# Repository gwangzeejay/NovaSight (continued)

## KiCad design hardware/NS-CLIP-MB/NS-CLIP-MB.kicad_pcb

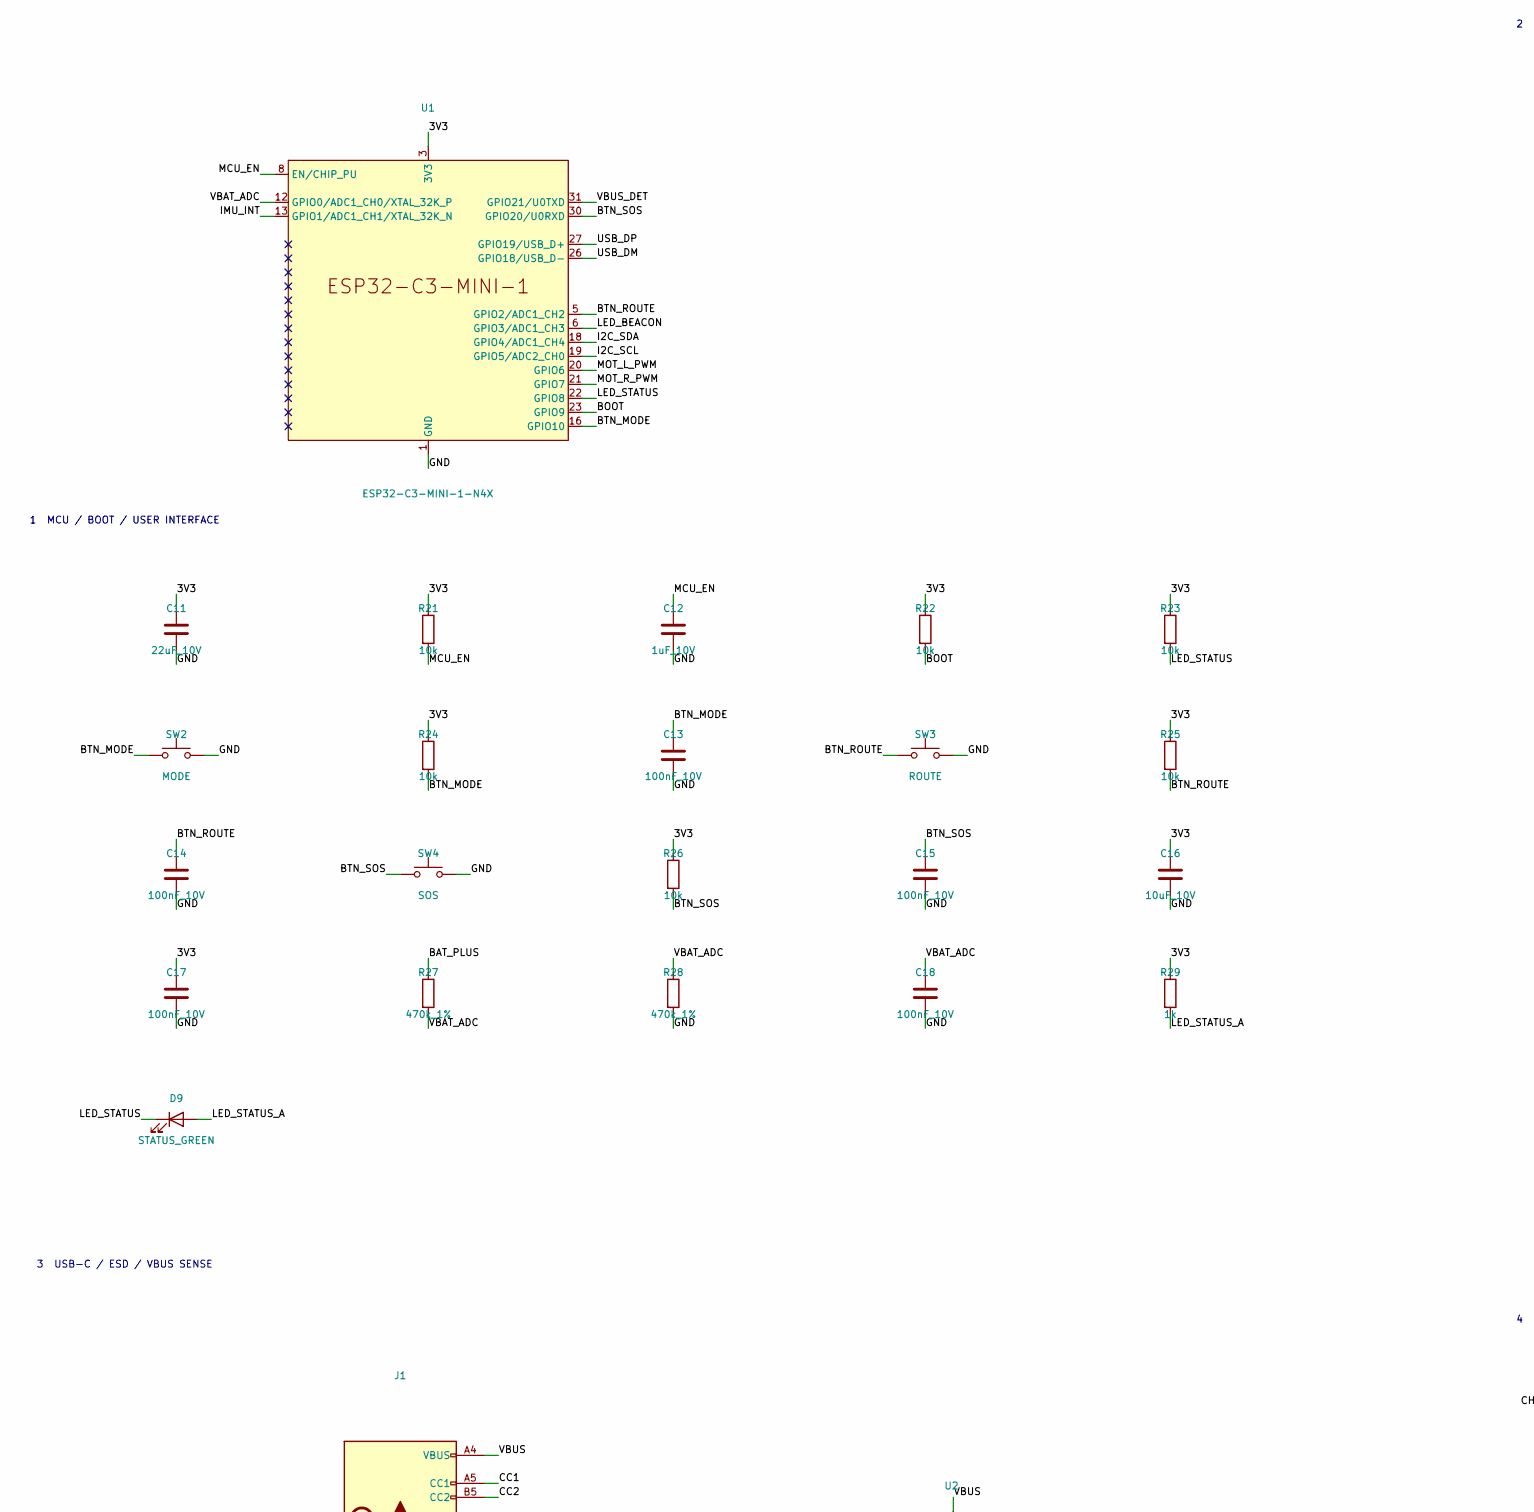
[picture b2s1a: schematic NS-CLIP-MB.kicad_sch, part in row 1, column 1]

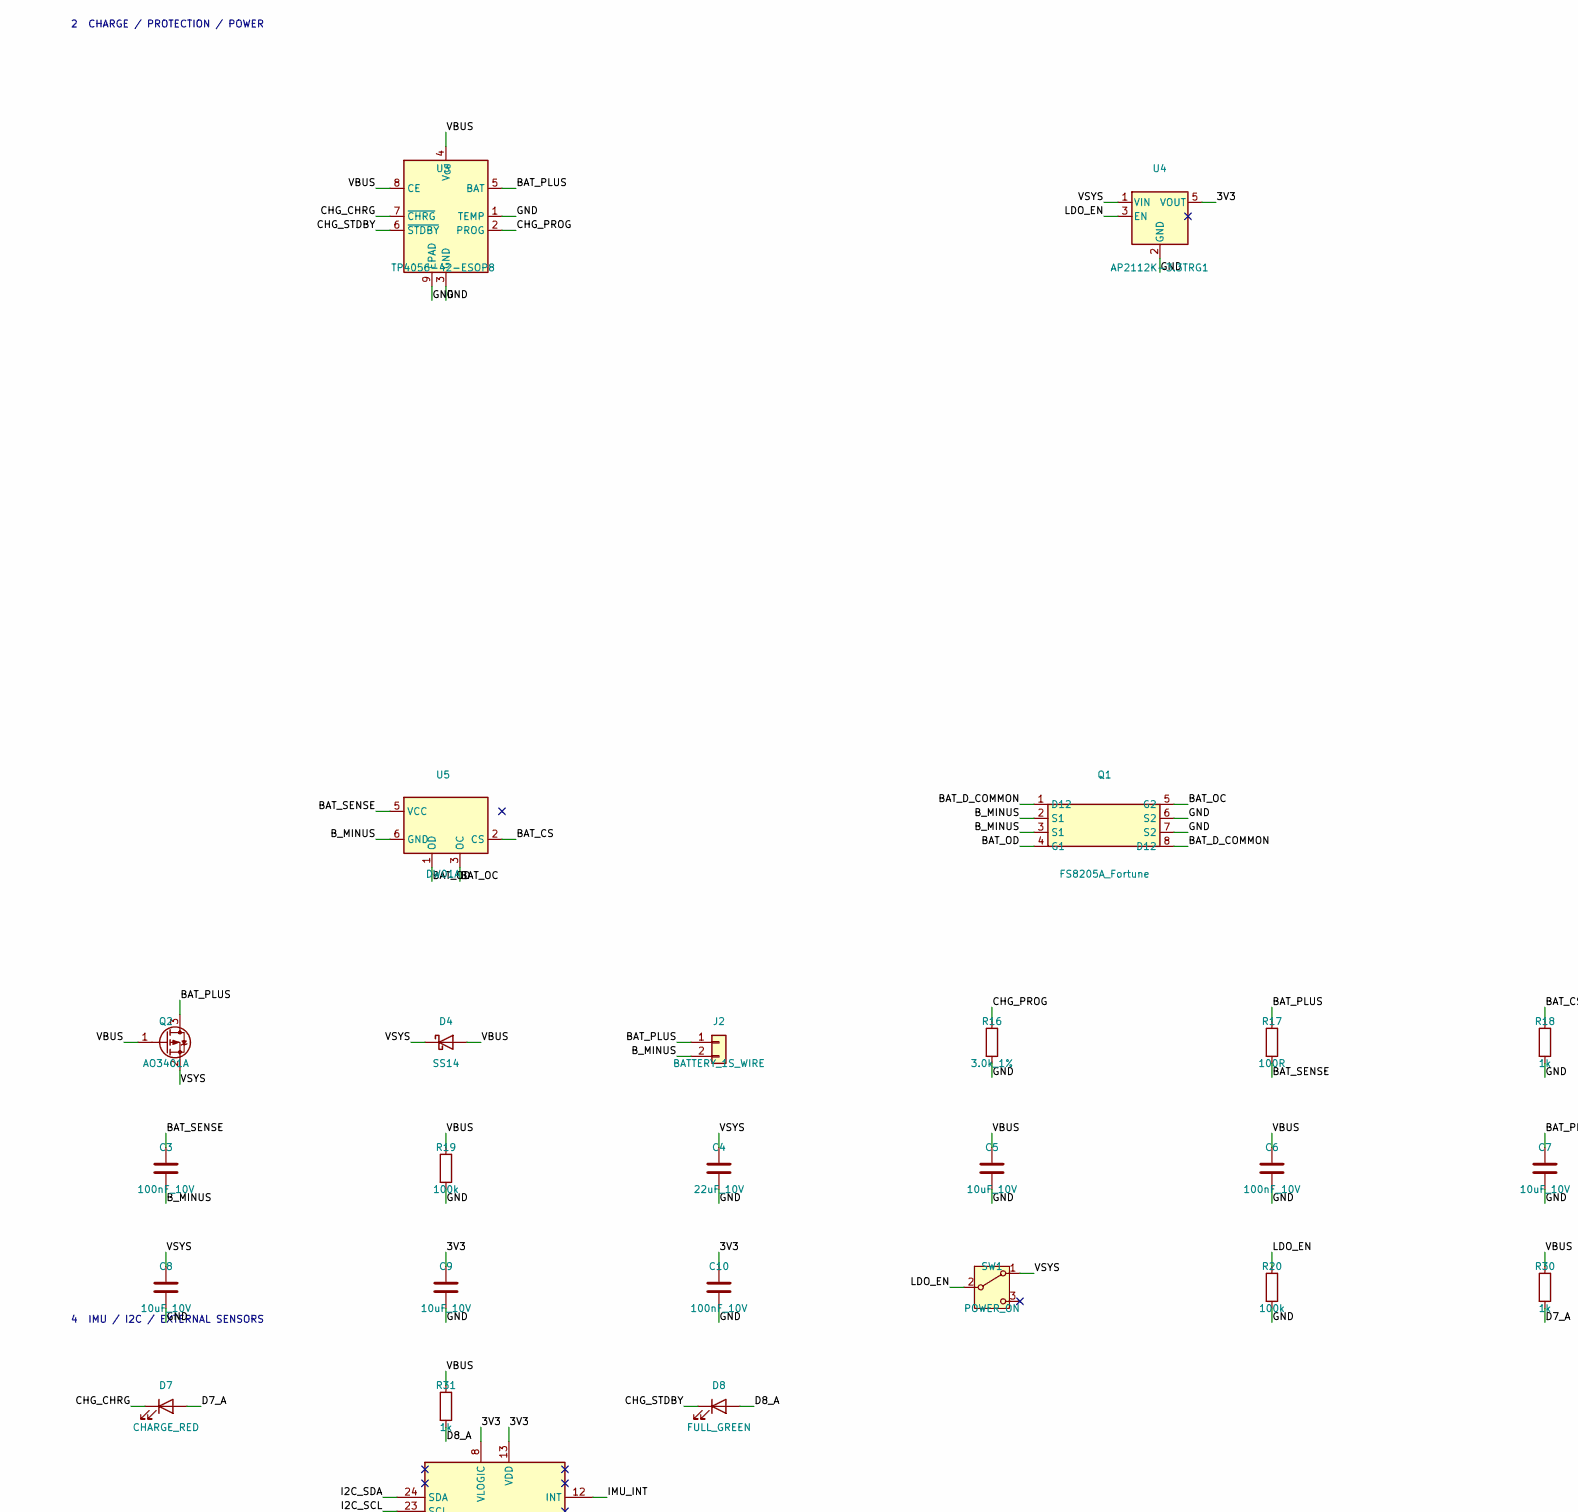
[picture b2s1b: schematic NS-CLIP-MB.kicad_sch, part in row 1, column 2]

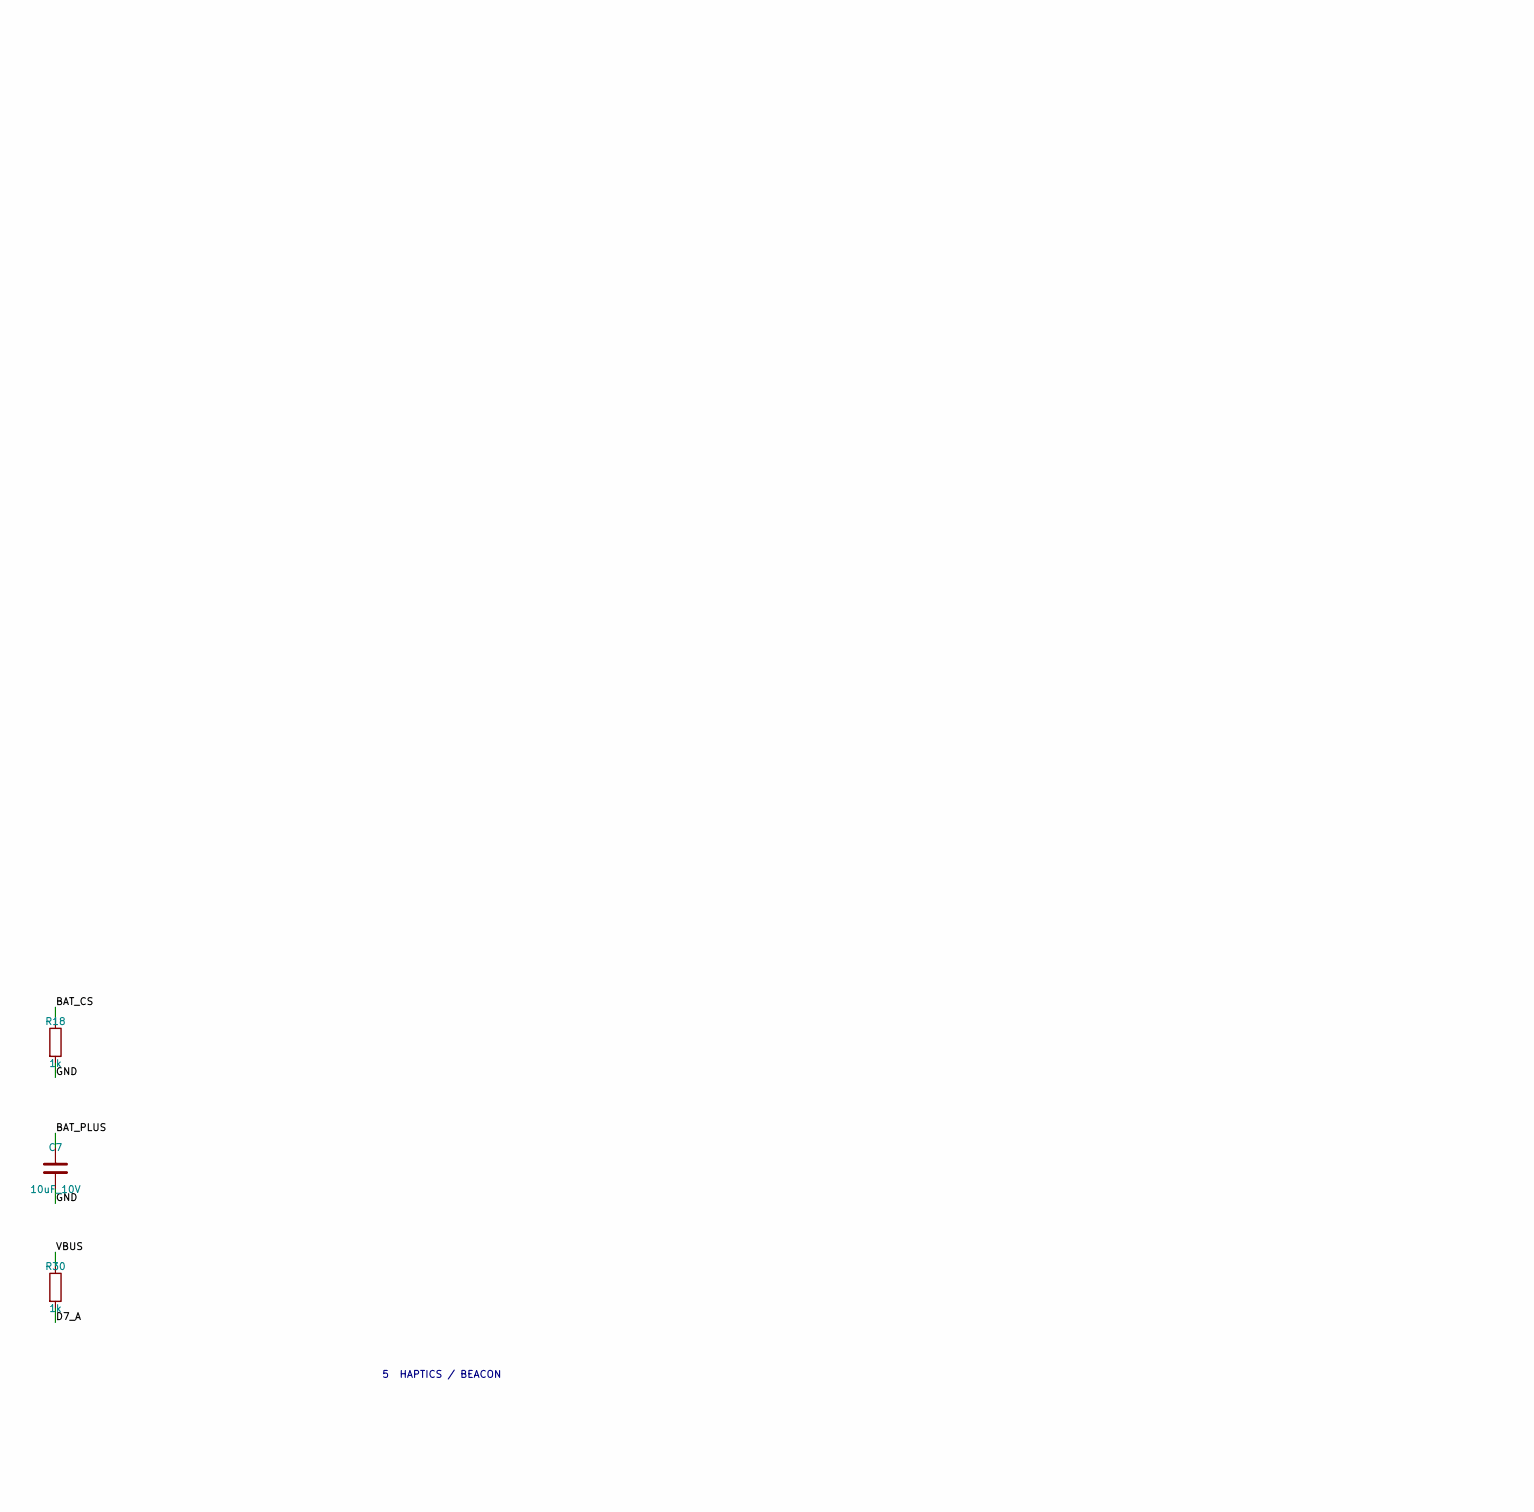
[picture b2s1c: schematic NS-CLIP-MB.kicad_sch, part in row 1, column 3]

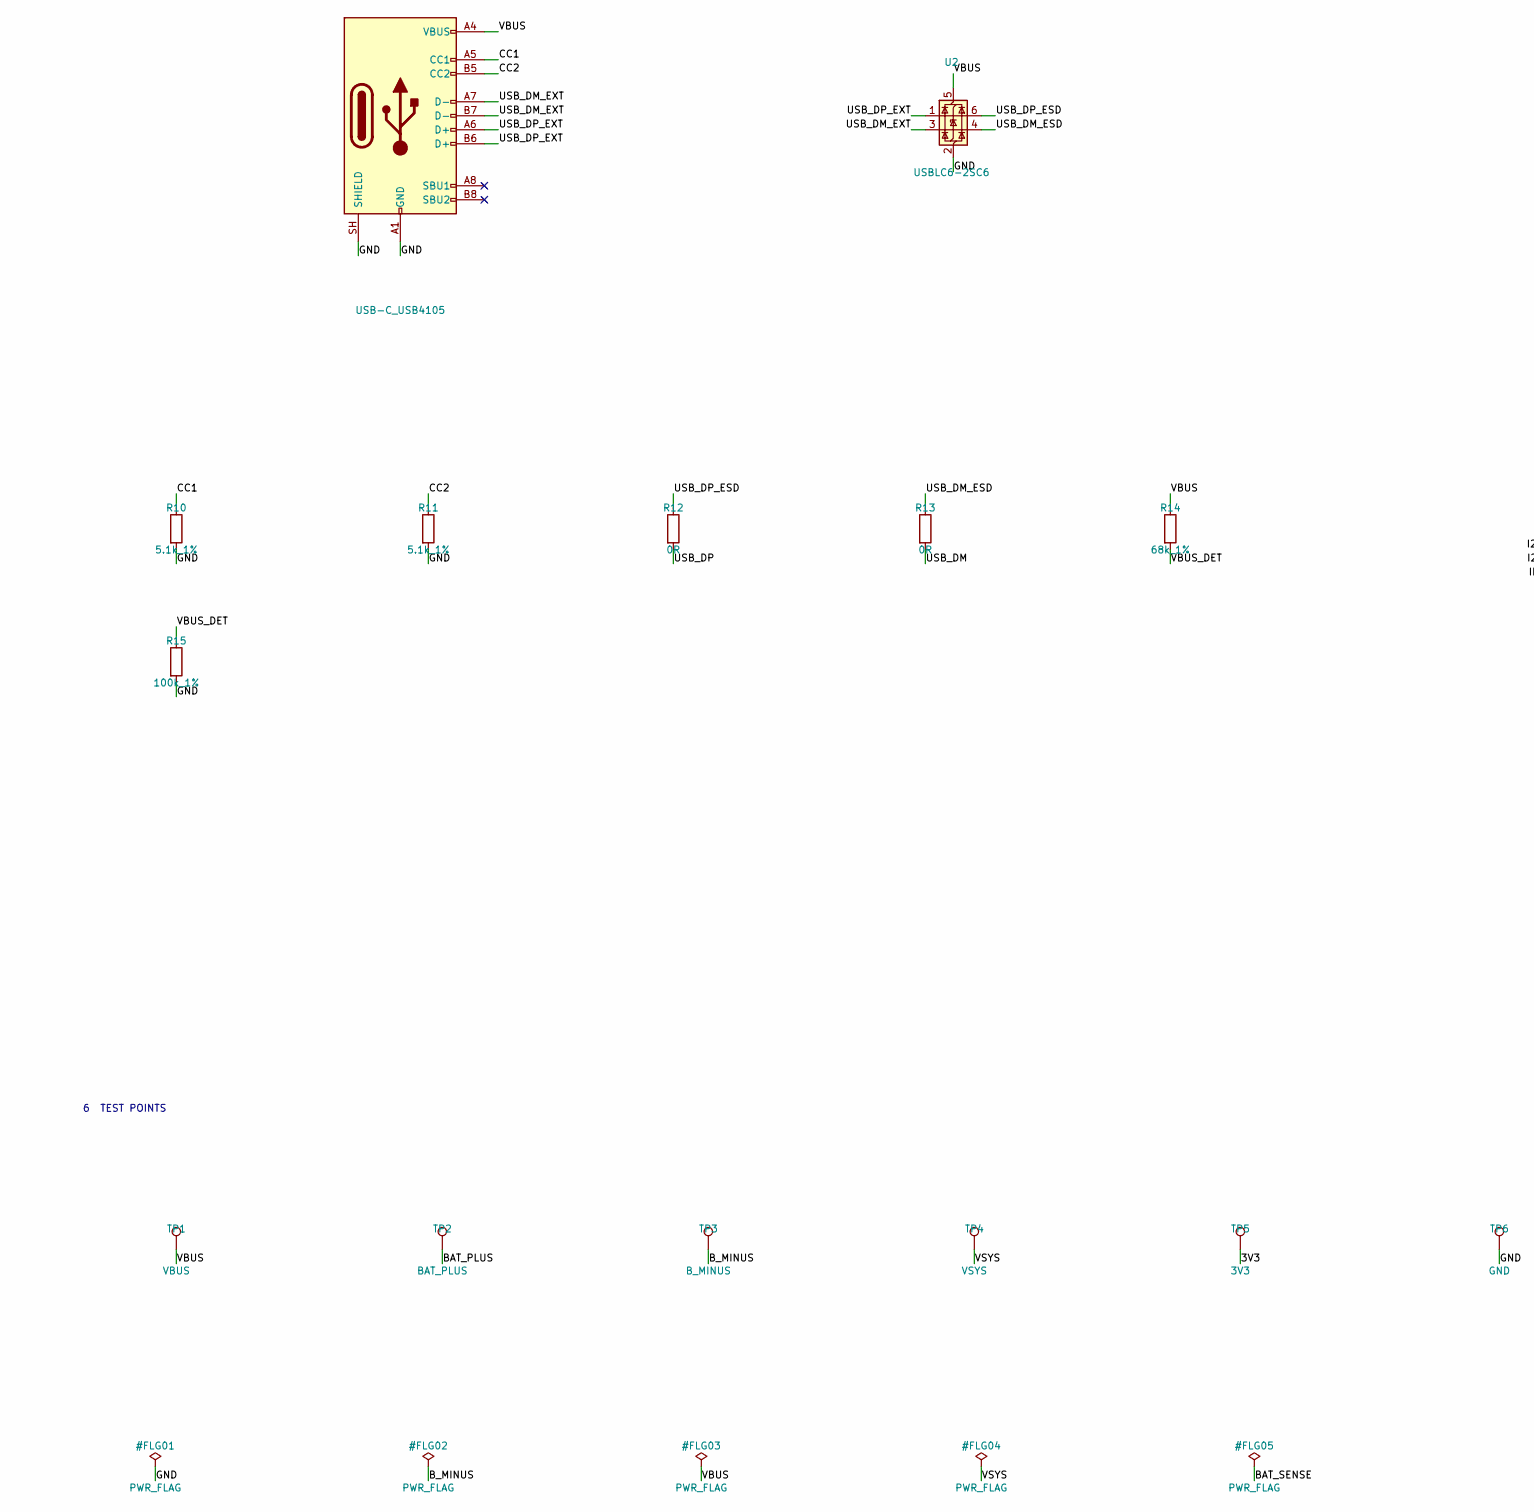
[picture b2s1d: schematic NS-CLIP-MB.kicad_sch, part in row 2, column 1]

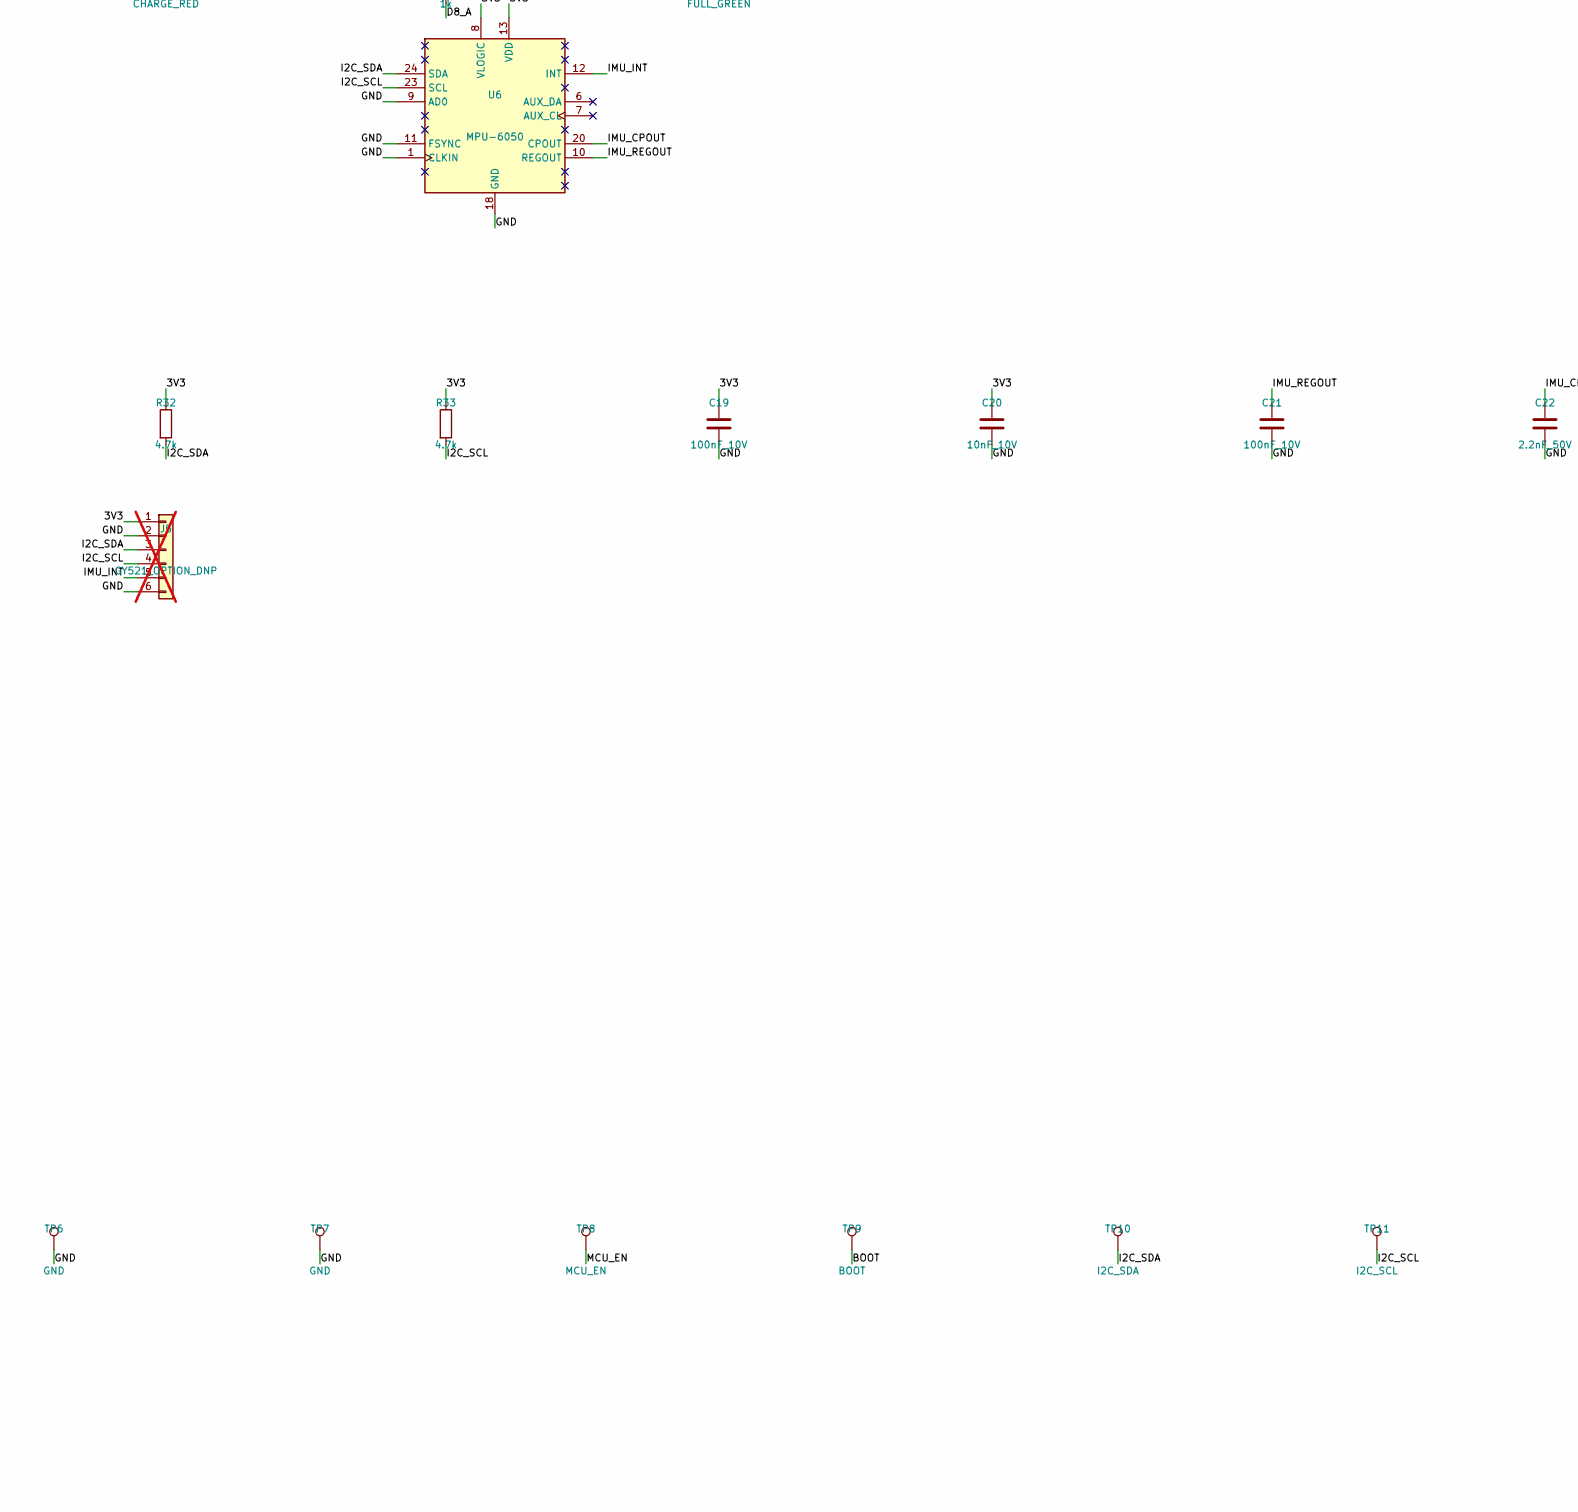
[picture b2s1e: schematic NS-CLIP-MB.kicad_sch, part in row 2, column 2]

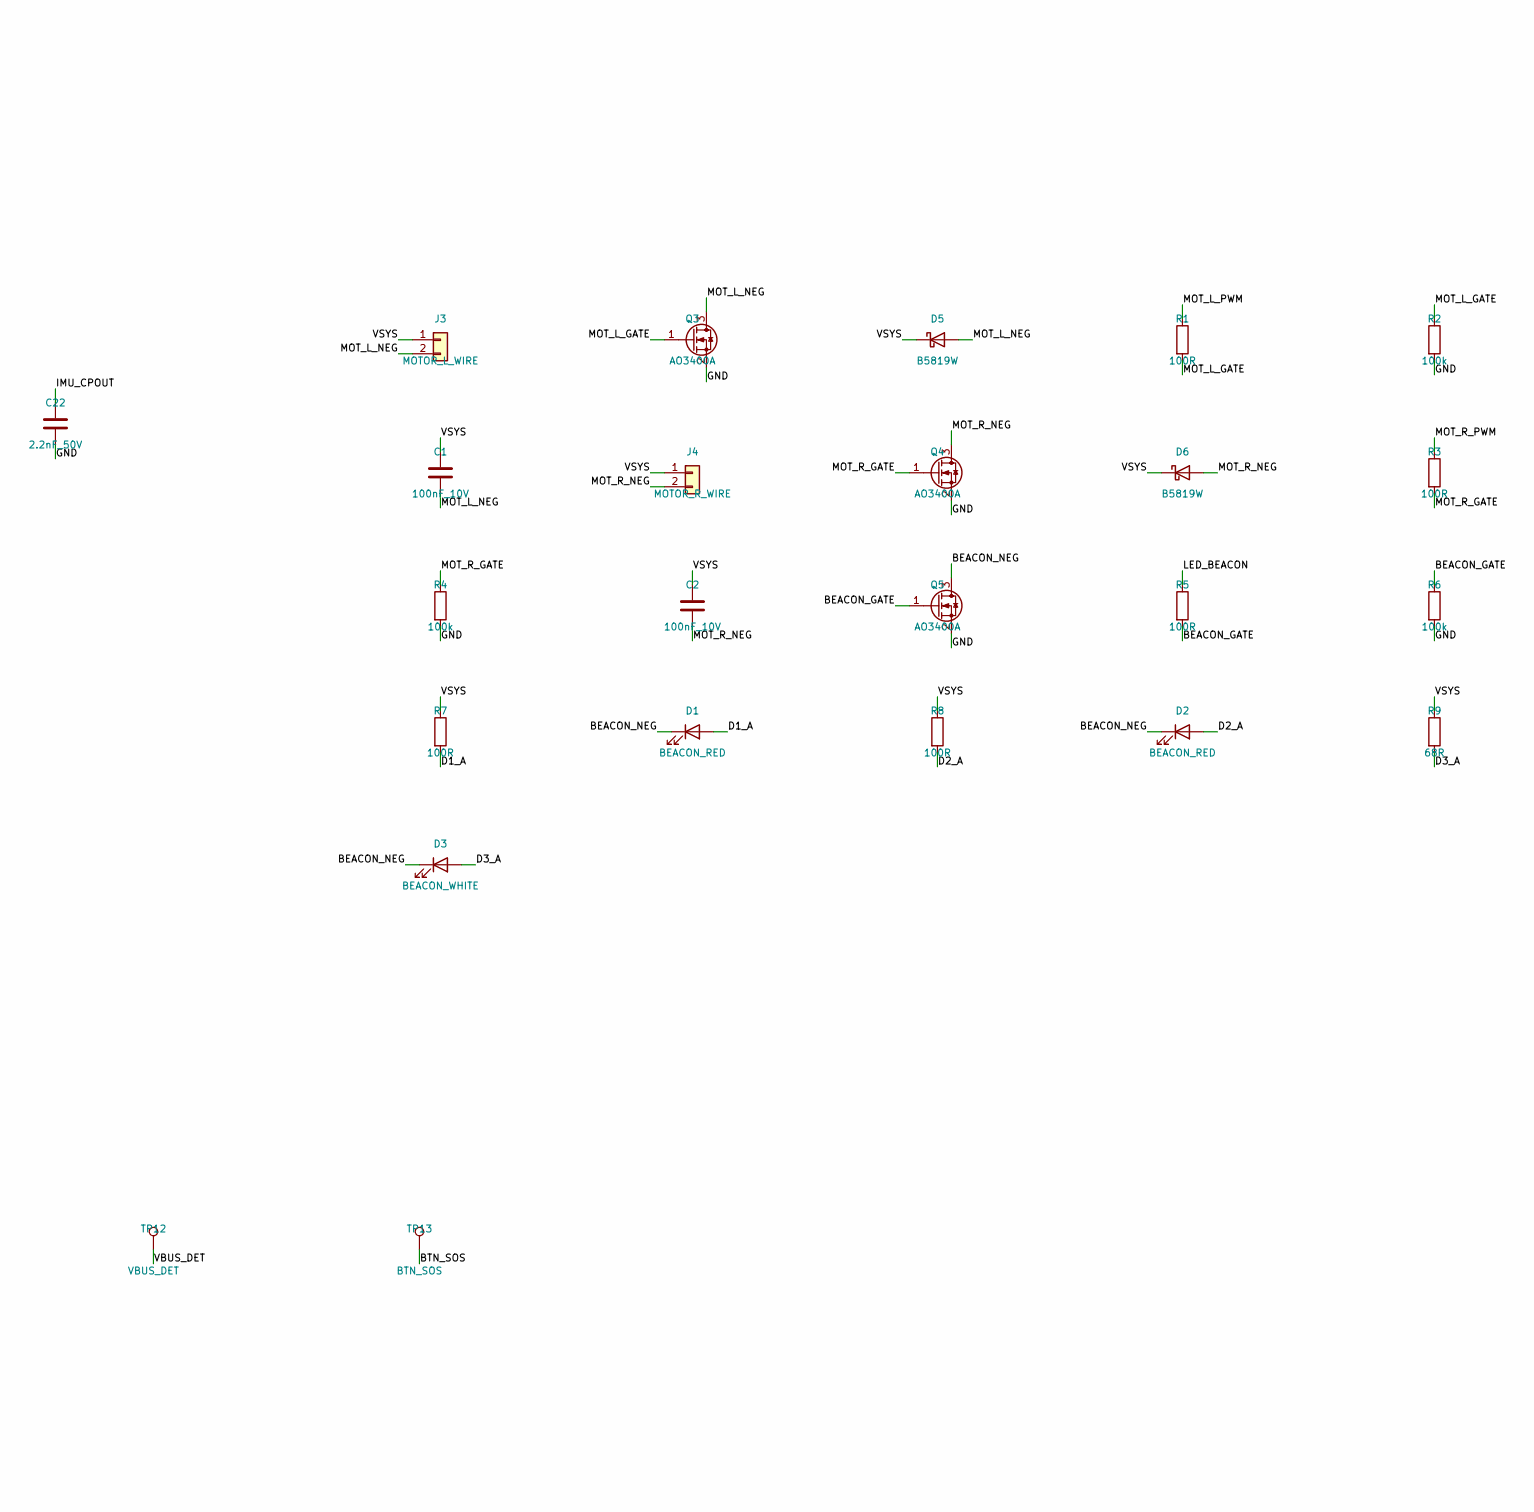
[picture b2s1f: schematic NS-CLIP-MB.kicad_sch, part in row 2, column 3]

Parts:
C1, C2, C3, C6, C10, C13, C14, C15, C17, C18, C19, C21: 100nF_10V; C_0402_1005Metric
C4, C11: 22uF_10V; C_0805_2012Metric
C5, C7, C8, C9, C16: 10uF_10V; C_0603_1608Metric
C12: 1uF_10V; C_0402_1005Metric
C20: 10nF_10V; C_0402_1005Metric
C22: 2.2nF_50V; C_0402_1005Metric
D1, D2: BEACON_RED; LED_D5.0mm
D3: BEACON_WHITE; LED_D5.0mm
D4: SS14; D_SMA
D5, D6: B5819W; D_SOD-123
D7: CHARGE_RED; LED_0603_1608Metric
D8: FULL_GREEN; LED_0603_1608Metric
D9: STATUS_GREEN; LED_0603_1608Metric
J1: USB-C_USB4105; USB_C_Receptacle_GCT_USB4105-xx-A_16P_TopMnt_Horizontal
J2: BATTERY_1S_WIRE; SolderWire-0.5sqmm_1x02_P4.6mm_D0.9mm_OD2.1mm
J3: MOTOR_L_WIRE; SolderWire-0.5sqmm_1x02_P4.6mm_D0.9mm_OD2.1mm
J4: MOTOR_R_WIRE; SolderWire-0.5sqmm_1x02_P4.6mm_D0.9mm_OD2.1mm
J5: GY521_OPTION_DNP; JST_SH_SM06B-SRSS-TB_1x06-1MP_P1.00mm_Horizontal; not fitted
Q1: FS8205A_Fortune; TSSOP-8_4.4x3mm_P0.65mm; LCSC C16052
Q2: AO3401A; SOT-23
Q3, Q4, Q5: AO3400A; SOT-23
R1, R3, R5, R17: 100R; R_0402_1005Metric
R2, R4, R6, R19, R20: 100k; R_0402_1005Metric
R7, R8: 100R; R_0603_1608Metric
R9: 68R; R_0603_1608Metric
R10, R11: 5.1k_1%; R_0402_1005Metric
R12, R13: 0R; R_0402_1005Metric
R14: 68k_1%; R_0402_1005Metric
R15: 100k_1%; R_0402_1005Metric
R16: 3.0k_1%; R_0402_1005Metric
R18, R29, R30, R31: 1k; R_0402_1005Metric
R21, R22, R23, R24, R25, R26: 10k; R_0402_1005Metric
R27, R28: 470k_1%; R_0402_1005Metric
R32, R33: 4.7k; R_0402_1005Metric
SW1: POWER_ON; SW_SPDT_Shouhan_MSK12C02
SW2: MODE; SW_SPST_EVQP2_ShortPushTravel_H2.5mm
SW3: ROUTE; SW_SPST_EVQP2_ShortPushTravel_H2.5mm
SW4: SOS; SW_SPST_EVQP2_ShortPushTravel_H2.5mm
TP1: VBUS; TestPoint_Pad_D1.0mm
TP2: BAT_PLUS; TestPoint_Pad_D1.0mm
TP3: B_MINUS; TestPoint_Pad_D1.0mm
TP4: VSYS; TestPoint_Pad_D1.0mm
TP5: 3V3; TestPoint_Pad_D1.0mm
TP6, TP7: GND; TestPoint_Pad_D1.0mm
TP8: MCU_EN; TestPoint_Pad_D1.0mm
TP9: BOOT; TestPoint_Pad_D1.0mm
TP10: I2C_SDA; TestPoint_Pad_D1.0mm
TP11: I2C_SCL; TestPoint_Pad_D1.0mm
TP12: VBUS_DET; TestPoint_Pad_D1.0mm
TP13: BTN_SOS; TestPoint_Pad_D1.0mm
U1: ESP32-C3-MINI-1-N4X; ESP32-C3-MINI-1
U2: USBLC6-2SC6; SOT-23-6
U3: TP4056-42-ESOP8; HSOP-8-1EP_3.9x4.9mm_P1.27mm_EP2.41x3.1mm
U4: AP2112K-3.3TRG1; SOT-23-5
U5: DW01A; SOT-23-6
U6: MPU-6050; InvenSense_QFN-24_4x4mm_P0.5mm; LCSC C24112

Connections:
/3V3: C9.1, C10.1, C11.1, C16.1, C17.1, C19.1, C20.1, J5.1, R21.1, R22.1, R23.1, R24.1, R25.1, R26.1, R29.1, R32.1, R33.1, TP5.1, U1.3 (3V3), U4.5 (VOUT), U6.8 (VLOGIC), U6.13 (VDD)
/BAT_CS: R18.1, U5.2 (CS)
/BAT_D_COMMON: Q1.1 (D12), Q1.8 (D12)
/BAT_OC: Q1.5 (G2), U5.3 (OC)
/BAT_OD: Q1.4 (G1), U5.1 (OD)
/BAT_PLUS: C7.1, J2.1, Q2.3 (D), R17.1, R27.1, TP2.1, U3.5 (BAT)
/BAT_SENSE: C3.1, R17.2, U5.5 (VCC)
/BEACON_GATE: Q5.1 (G), R5.2, R6.1
/BEACON_NEG: D1.1 (K), D2.1 (K), D3.1 (K), Q5.3 (D)
/BOOT: R22.2, TP9.1, U1.23 (GPIO9)
/BTN_MODE: C13.1, R24.2, SW2.1, U1.16 (GPIO10)
/BTN_ROUTE: C14.1, R25.2, SW3.1, U1.5 (GPIO2/ADC1_CH2)
/BTN_SOS: C15.1, R26.2, SW4.1, TP13.1, U1.30 (GPIO20/U0RXD)
/B_MINUS: C3.2, J2.2, Q1.2 (S1), Q1.3 (S1), TP3.1, U5.6 (GND)
/CC1: J1.A5 (CC1), R10.1
/CC2: J1.B5 (CC2), R11.1
/CHG_CHRG: D7.1 (K), U3.7 (~CHRG)
/CHG_PROG: R16.1, U3.2 (PROG)
/CHG_STDBY: D8.1 (K), U3.6 (~STDBY)
/D1_A: D1.2 (A), R7.2
/D2_A: D2.2 (A), R8.2
/D3_A: D3.2 (A), R9.2
/D7_A: D7.2 (A), R30.2
/D8_A: D8.2 (A), R31.2
/GND: C4.2, C5.2, C6.2, C7.2, C8.2, C9.2, C10.2, C11.2, C12.2, C13.2, C14.2, C15.2, C16.2, C17.2, C18.2, C19.2, C20.2, C21.2, C22.2, J1.A1 (GND), J1.A12 (GND), J1.B1 (GND), J1.B12 (GND), J1.SH (SHIELD), J5.2, J5.6, Q1.6 (S2), Q1.7 (S2), Q3.2 (S), Q4.2 (S), Q5.2 (S), R2.2, R4.2, R6.2, R10.2, R11.2, R15.2, R16.2, R18.2, R19.2, R20.2, R28.2, SW2.2, SW3.2, SW4.2, TP6.1, TP7.1, U1.1 (GND), U1.2 (GND), U1.11 (GND), U1.14 (GND), U1.36 (GND), U1.37 (GND), U1.38 (GND), U1.39 (GND), U1.40 (GND), U1.41 (GND), U1.42 (GND), U1.43 (GND), U1.44 (GND), U1.45 (GND), U1.46 (GND), U1.47 (GND), U1.48 (GND), U1.49 (GND), U1.50 (GND), U1.51 (GND), U1.52 (GND), U1.53 (GND), U2.2 (GND), U3.1 (TEMP), U3.3 (GND), U3.9 (EPAD), U4.2 (GND), U6.1 (CLKIN), U6.9 (AD0), U6.11 (FSYNC), U6.18 (GND)
/I2C_SCL: J5.4, R33.2, TP11.1, U1.19 (GPIO5/ADC2_CH0), U6.23 (SCL)
/I2C_SDA: J5.3, R32.2, TP10.1, U1.18 (GPIO4/ADC1_CH4), U6.24 (SDA)
/IMU_CPOUT: C22.1, U6.20 (CPOUT)
/IMU_INT: J5.5, U1.13 (GPIO1/ADC1_CH1/XTAL_32K_N), U6.12 (INT)
/IMU_REGOUT: C21.1, U6.10 (REGOUT)
/LDO_EN: R20.1, SW1.2 (B), U4.3 (EN)
/LED_BEACON: R5.1, U1.6 (GPIO3/ADC1_CH3)
/LED_STATUS: D9.1 (K), R23.2, U1.22 (GPIO8)
/LED_STATUS_A: D9.2 (A), R29.2
/MCU_EN: C12.1, R21.2, TP8.1, U1.8 (EN/CHIP_PU)
/MOT_L_GATE: Q3.1 (G), R1.2, R2.1
/MOT_L_NEG: C1.2, D5.2 (A), J3.2, Q3.3 (D)
/MOT_L_PWM: R1.1, U1.20 (GPIO6)
/MOT_R_GATE: Q4.1 (G), R3.2, R4.1
/MOT_R_NEG: C2.2, D6.2 (A), J4.2, Q4.3 (D)
/MOT_R_PWM: R3.1, U1.21 (GPIO7)
/USB_DM: R13.2, U1.26 (GPIO18/USB_D-)
/USB_DM_ESD: R13.1, U2.4 (I/O2)
/USB_DM_EXT: J1.A7 (D-), J1.B7 (D-), U2.3 (I/O2)
/USB_DP: R12.2, U1.27 (GPIO19/USB_D+)
/USB_DP_ESD: R12.1, U2.6 (I/O1)
/USB_DP_EXT: J1.A6 (D+), J1.B6 (D+), U2.1 (I/O1)
/VBAT_ADC: C18.1, R27.2, R28.1, U1.12 (GPIO0/ADC1_CH0/XTAL_32K_P)
/VBUS: C5.1, C6.1, D4.2 (A), J1.A4 (VBUS), J1.A9 (VBUS), J1.B4 (VBUS), J1.B9 (VBUS), Q2.1 (G), R14.1, R19.1, R30.1, R31.1, TP1.1, U2.5 (VBUS), U3.4 (V_{CC}), U3.8 (CE)
/VBUS_DET: R14.2, R15.1, TP12.1, U1.31 (GPIO21/U0TXD)
/VSYS: C1.1, C2.1, C4.1, C8.1, D4.1 (K), D5.1 (K), D6.1 (K), J3.1, J4.1, Q2.2 (S), R7.1, R8.1, R9.1, SW1.1 (A), TP4.1, U4.1 (VIN)

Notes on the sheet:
5 HAPTICS / BEACON
2 CHARGE / PROTECTION / POWER
3 USB-C / ESD / VBUS SENSE
4 IMU / I2C / EXTERNAL SENSORS
1 MCU / BOOT / USER INTERFACE
6 TEST POINTS

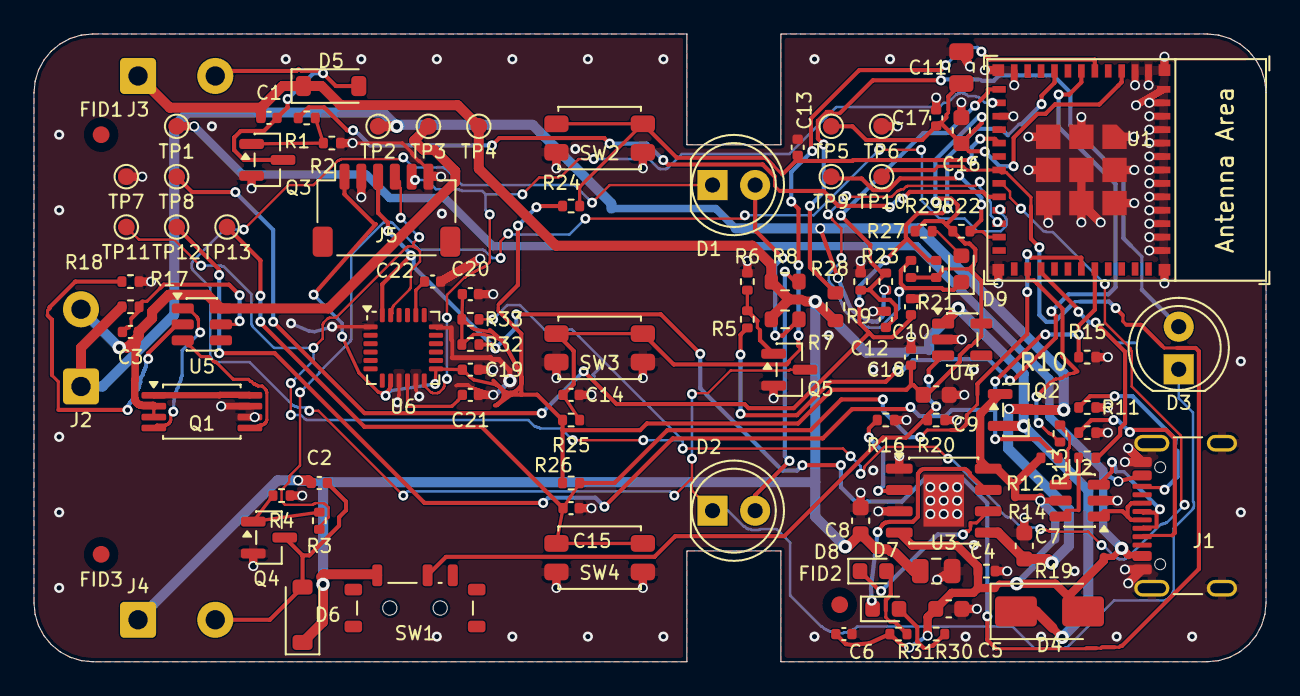
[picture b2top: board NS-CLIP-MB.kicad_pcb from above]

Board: 2 copper layers, 73.4 x 37.4 mm, 100 parts (0 on the bottom side), 51 nets.

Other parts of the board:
FID1, FID2, FID3: FIDUCIAL; Fiducial_1mm_Mask2mm

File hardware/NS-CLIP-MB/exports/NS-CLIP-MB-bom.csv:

"Refs","Value","Footprint","Qty","DNP"
"C1","100nF_10V","Capacitor_SMD:C_0402_1005Metric","1",""
"C2","100nF_10V","Capacitor_SMD:C_0402_1005Metric","1",""
"C3","100nF_10V","Capacitor_SMD:C_0402_1005Metric","1",""
"C4","22uF_10V","Capacitor_SMD:C_0805_2012Metric","1",""
"C5","10uF_10V","Capacitor_SMD:C_0603_1608Metric","1",""
"C6","100nF_10V","Capacitor_SMD:C_0402_1005Metric","1",""
"C7","10uF_10V","Capacitor_SMD:C_0603_1608Metric","1",""
"C8","10uF_10V","Capacitor_SMD:C_0603_1608Metric","1",""
"C9","10uF_10V","Capacitor_SMD:C_0603_1608Metric","1",""
"C10","100nF_10V","Capacitor_SMD:C_0402_1005Metric","1",""
"C11","22uF_10V","Capacitor_SMD:C_0805_2012Metric","1",""
"C12","1uF_10V","Capacitor_SMD:C_0402_1005Metric","1",""
"C13","100nF_10V","Capacitor_SMD:C_0402_1005Metric","1",""
"C14","100nF_10V","Capacitor_SMD:C_0402_1005Metric","1",""
"C15","100nF_10V","Capacitor_SMD:C_0402_1005Metric","1",""
"C16","10uF_10V","Capacitor_SMD:C_0603_1608Metric","1",""
"C17","100nF_10V","Capacitor_SMD:C_0402_1005Metric","1",""
"C18","100nF_10V","Capacitor_SMD:C_0402_1005Metric","1",""
"C19","100nF_10V","Capacitor_SMD:C_0402_1005Metric","1",""
"C20","10nF_10V","Capacitor_SMD:C_0402_1005Metric","1",""
"C21","100nF_10V","Capacitor_SMD:C_0402_1005Metric","1",""
"C22","2.2nF_50V","Capacitor_SMD:C_0402_1005Metric","1",""
"D1","BEACON_RED","LED_THT:LED_D5.0mm","1",""
"D2","BEACON_RED","LED_THT:LED_D5.0mm","1",""
"D3","BEACON_WHITE","LED_THT:LED_D5.0mm","1",""
"D4","SS14","Diode_SMD:D_SMA","1",""
"D5","B5819W","Diode_SMD:D_SOD-123","1",""
"D6","B5819W","Diode_SMD:D_SOD-123","1",""
"D7","CHARGE_RED","LED_SMD:LED_0603_1608Metric","1",""
"D8","FULL_GREEN","LED_SMD:LED_0603_1608Metric","1",""
"D9","STATUS_GREEN","LED_SMD:LED_0603_1608Metric","1",""
"J1","USB-C_USB4105","Connector_USB:USB_C_Receptacle_GCT_USB4105-xx-A_16P_TopMnt_Horizontal","1",""
"J2","BATTERY_1S_WIRE","Connector_Wire:SolderWire-0.5sqmm_1x02_P4.6mm_D0.9mm_OD2.1mm","1",""
"J3","MOTOR_L_WIRE","Connector_Wire:SolderWire-0.5sqmm_1x02_P4.6mm_D0.9mm_OD2.1mm","1",""
"J4","MOTOR_R_WIRE","Connector_Wire:SolderWire-0.5sqmm_1x02_P4.6mm_D0.9mm_OD2.1mm","1",""
"J5","GY521_OPTION_DNP","Connector_JST:JST_SH_SM06B-SRSS-TB_1x06-1MP_P1.00mm_Horizontal","1","DNP"
"Q1","FS8205A_Fortune","Package_SO:TSSOP-8_3x3mm_P0.65mm","1",""
"Q2","AO3401A","Package_TO_SOT_SMD:SOT-23","1",""
"Q3","AO3400A","Package_TO_SOT_SMD:SOT-23","1",""
"Q4","AO3400A","Package_TO_SOT_SMD:SOT-23","1",""
"Q5","AO3400A","Package_TO_SOT_SMD:SOT-23","1",""
"R1","100R","Resistor_SMD:R_0402_1005Metric","1",""
"R2","100k","Resistor_SMD:R_0402_1005Metric","1",""
"R3","100R","Resistor_SMD:R_0402_1005Metric","1",""
"R4","100k","Resistor_SMD:R_0402_1005Metric","1",""
"R5","100R","Resistor_SMD:R_0402_1005Metric","1",""
"R6","100k","Resistor_SMD:R_0402_1005Metric","1",""
"R7","100R","Resistor_SMD:R_0603_1608Metric","1",""
"R8","100R","Resistor_SMD:R_0603_1608Metric","1",""
"R9","68R","Resistor_SMD:R_0603_1608Metric","1",""
"R10","5.1k_1%","Resistor_SMD:R_0402_1005Metric","1",""
"R11","5.1k_1%","Resistor_SMD:R_0402_1005Metric","1",""
"R12","0R","Resistor_SMD:R_0402_1005Metric","1",""
"R13","0R","Resistor_SMD:R_0402_1005Metric","1",""
"R14","68k_1%","Resistor_SMD:R_0402_1005Metric","1",""
"R15","100k_1%","Resistor_SMD:R_0402_1005Metric","1",""
"R16","3.0k_1%","Resistor_SMD:R_0402_1005Metric","1",""
"R17","100R","Resistor_SMD:R_0402_1005Metric","1",""
"R18","1k","Resistor_SMD:R_0402_1005Metric","1",""
"R19","100k","Resistor_SMD:R_0402_1005Metric","1",""
"R20","100k","Resistor_SMD:R_0402_1005Metric","1",""
"R21","10k","Resistor_SMD:R_0402_1005Metric","1",""
"R22","10k","Resistor_SMD:R_0402_1005Metric","1",""
"R23","10k","Resistor_SMD:R_0402_1005Metric","1",""
"R24","10k","Resistor_SMD:R_0402_1005Metric","1",""
"R25","10k","Resistor_SMD:R_0402_1005Metric","1",""
"R26","10k","Resistor_SMD:R_0402_1005Metric","1",""
"R27","470k_1%","Resistor_SMD:R_0402_1005Metric","1",""
"R28","470k_1%","Resistor_SMD:R_0402_1005Metric","1",""
"R29","1k","Resistor_SMD:R_0402_1005Metric","1",""
"R30","1k","Resistor_SMD:R_0402_1005Metric","1",""
"R31","1k","Resistor_SMD:R_0402_1005Metric","1",""
"R32","4.7k","Resistor_SMD:R_0402_1005Metric","1",""
"R33","4.7k","Resistor_SMD:R_0402_1005Metric","1",""
"SW1","POWER_ON","Button_Switch_SMD:SW_SPDT_Shouhan_MSK12C02","1",""
"SW2","MODE","Button_Switch_SMD:SW_SPST_EVQP2_ShortPushTravel_H2.5mm","1",""
"SW3","ROUTE","Button_Switch_SMD:SW_SPST_EVQP2_ShortPushTravel_H2.5mm","1",""
"SW4","SOS","Button_Switch_SMD:SW_SPST_EVQP2_ShortPushTravel_H2.5mm","1",""
"TP1","VBUS","TestPoint:TestPoint_Pad_D1.0mm","1",""
"TP2","BAT_PLUS","TestPoint:TestPoint_Pad_D1.0mm","1",""
"TP3","B_MINUS","TestPoint:TestPoint_Pad_D1.0mm","1",""
"TP4","VSYS","TestPoint:TestPoint_Pad_D1.0mm","1",""
"TP5","3V3","TestPoint:TestPoint_Pad_D1.0mm","1",""
"TP6","GND","TestPoint:TestPoint_Pad_D1.0mm","1",""
"TP7","GND","TestPoint:TestPoint_Pad_D1.0mm","1",""
"TP8","MCU_EN","TestPoint:TestPoint_Pad_D1.0mm","1",""
"TP9","BOOT","TestPoint:TestPoint_Pad_D1.0mm","1",""
"TP10","I2C_SDA","TestPoint:TestPoint_Pad_D1.0mm","1",""
"TP11","I2C_SCL","TestPoint:TestPoint_Pad_D1.0mm","1",""
"TP12","VBUS_DET","TestPoint:TestPoint_Pad_D1.0mm","1",""
"TP13","BTN_SOS","TestPoint:TestPoint_Pad_D1.0mm","1",""
"U1","ESP32-C3-MINI-1-N4X","Espressif:ESP32-C3-MINI-1","1",""
"U2","USBLC6-2SC6","Package_TO_SOT_SMD:SOT-23-6","1",""
"U3","TP4056-42-ESOP8","Package_SO:HSOP-8-1EP_3.9x4.9mm_P1.27mm_EP2.41x3.1mm","1",""
"U4","AP2112K-3.3TRG1","Package_TO_SOT_SMD:SOT-23-5","1",""
"U5","DW01A","Package_TO_SOT_SMD:SOT-23-6","1",""
"U6","MPU-6050","Sensor_Motion:InvenSense_QFN-24_4x4mm_P0.5mm","1",""
